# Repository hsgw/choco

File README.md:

# CHOCO

7x4 ortholinear onehanded keyboard/macropad.   

- kailh choc switch (pg1350)
- USB type-c
- STM32F072C8T6
- QMK Firmware - https://github.com/hsgw/qmk_firmware/tree/choco

## BUILD
### Cut mounting leg (SW_CHOC6)

### How to enter bootloader
1. Push and hold reset switch
2. Push and hold boot switch (SW_CHOC7 / right upper corner switch)
3. Release reset switch
4. Release boot switch

### Firmware
QMK Firmware - https://github.com/hsgw/qmk_firmware/tree/choco

## License
MIT license   
(c)2019 Takuya Urakawa, Dm9Records

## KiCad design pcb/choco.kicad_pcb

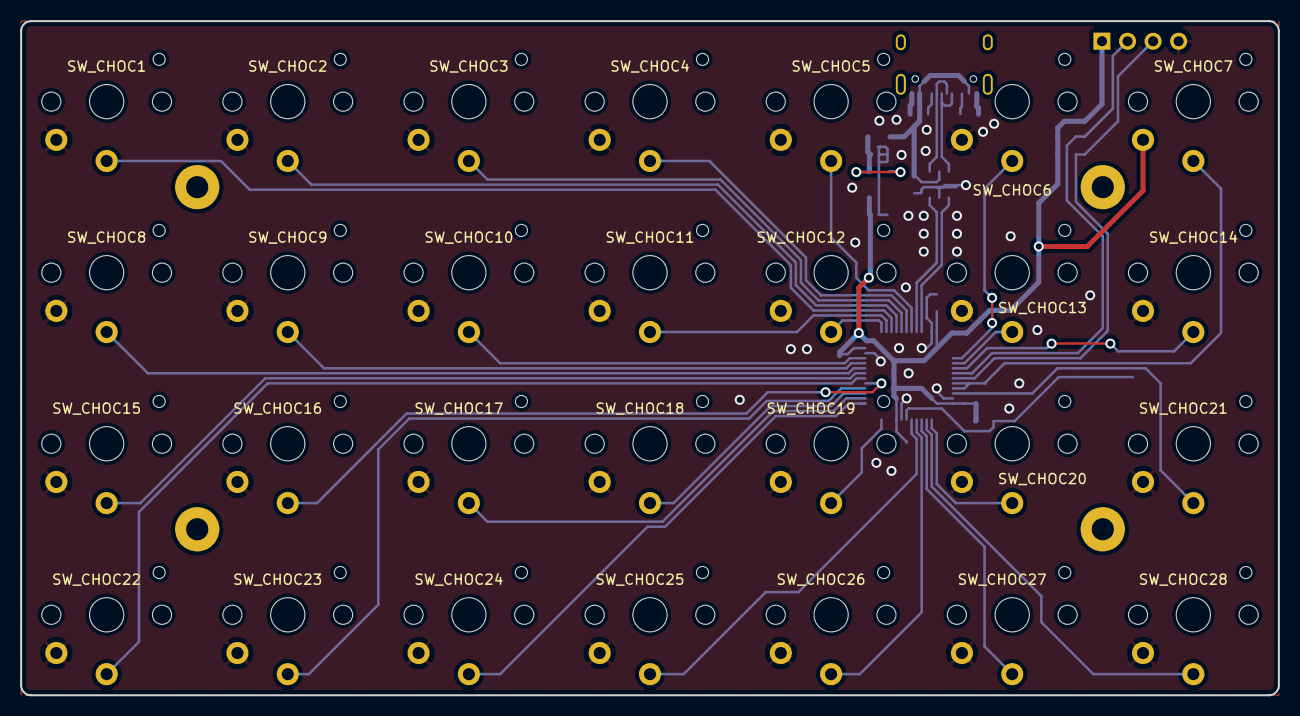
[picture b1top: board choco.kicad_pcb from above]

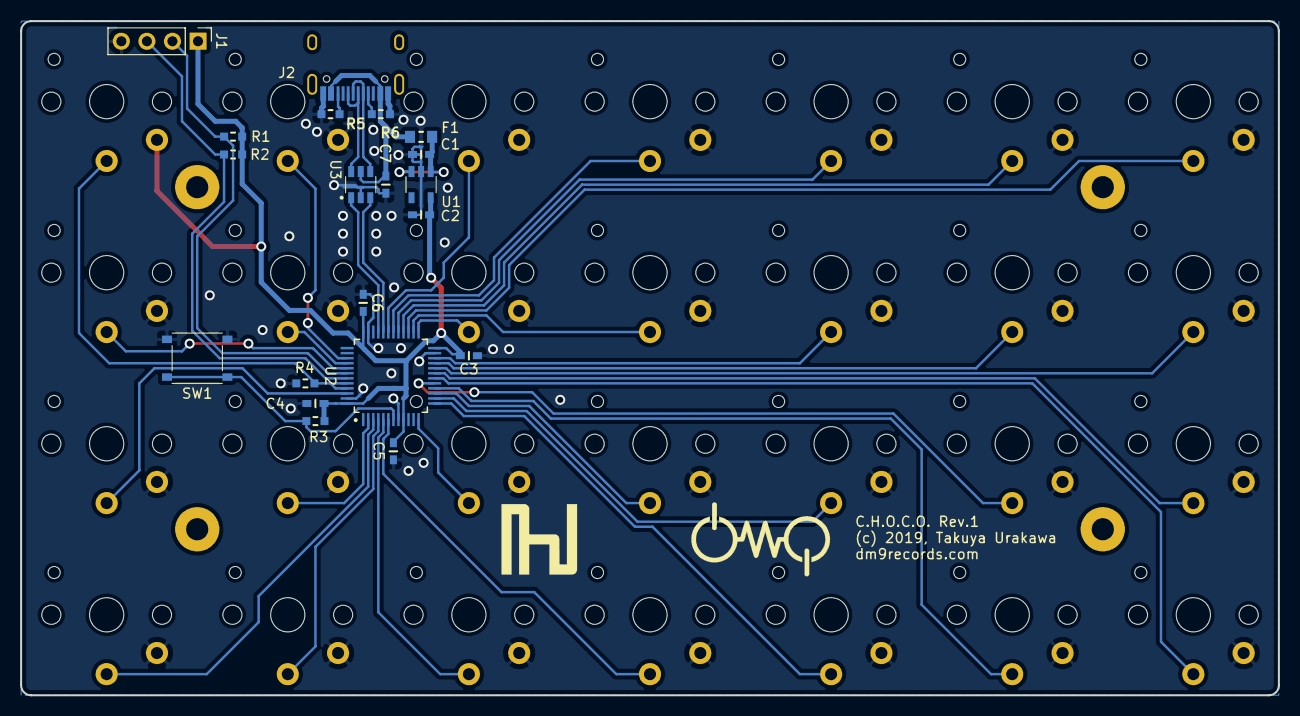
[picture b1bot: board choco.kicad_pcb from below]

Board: 2 copper layers, 125.0 x 67.0 mm, 48 parts (20 on the bottom side), 41 nets.

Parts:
C1, C2: 1u; C1608_Hand
C3, C4, C5, C6, C7: 0.1u; C1608_Hand
F1: 100mA; C2012_hand
J1: Conn_01x04; Socket_Strip_Straight_1x04_Pitch2.54mm
J2: USB_C_12pin_Receptacle; HRO-TYPE-C-31-M-12-Assembly
R1, R2: I2C; R1608_Hand
R3, R4: 10k; R1608_Hand
R5, R6: 5.1k; R1608_Hand
SW1: SW_Push; TACT_5.1x5.1
SW_CHOC1, SW_CHOC2, SW_CHOC3, SW_CHOC4, SW_CHOC5, SW_CHOC6, SW_CHOC7, SW_CHOC8, SW_CHOC9, SW_CHOC10, SW_CHOC11, SW_CHOC12, SW_CHOC13, SW_CHOC14, SW_CHOC15, SW_CHOC16, SW_CHOC17, SW_CHOC18, SW_CHOC19, SW_CHOC20, SW_CHOC21, SW_CHOC22, SW_CHOC23, SW_CHOC24, SW_CHOC25, SW_CHOC26, SW_CHOC27, SW_CHOC28: SW_Push; SW_kailh_pg1350_1u
U1: TLV73333PDBVR; SOT-23-5
U2: STM32F072C8Tx; LQFP-48_7x7mm_Pitch0.5mm
U3: USBLC6-2SC6; SOT-23-6

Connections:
+3V3: C2.1, C3.1, C4.1, C5.1, C6.1, J1.1, R1.1, R2.1, R3.1, SW_CHOC7.2, U1.5, U2.9, U2.24, U2.36, U2.48
/BOOT: R4.1, SW_CHOC7.1, U2.44, U2.45
/I2C_SCL: J1.2, R1.2, U2.42
/I2C_SDA: J1.3, R2.2, U2.43
/SW1: SW_CHOC1.1, U2.27
/SW2: SW_CHOC2.1, U2.28
/SW3: SW_CHOC3.1, U2.29
/SW4: SW_CHOC4.1, U2.30
/SW5: SW_CHOC5.1, U2.31
/SW6: SW_CHOC6.1, U2.39
/SW8: SW_CHOC8.1, U2.20
/SW9: SW_CHOC9.1, U2.21
/SW10: SW_CHOC10.1, U2.22
/SW11: SW_CHOC11.1, U2.26
/SW12: SW_CHOC12.1, U2.25
/SW13: SW_CHOC13.1, U2.40
/SW14: SW_CHOC14.1, U2.41
/SW15: SW_CHOC15.1, U2.19
/SW16: SW_CHOC16.1, U2.17
/SW17: SW_CHOC17.1, U2.14
/SW18: SW_CHOC18.1, U2.15
/SW19: SW_CHOC19.1, U2.12
/SW20: SW_CHOC20.1, U2.2
/SW21: SW_CHOC21.1, U2.46
/SW22: SW_CHOC22.1, U2.18
/SW23: SW_CHOC23.1, U2.16
/SW24: SW_CHOC24.1, U2.13
/SW25: SW_CHOC25.1, U2.6
/SW26: SW_CHOC26.1, U2.5
/SW27: SW_CHOC27.1, U2.4
/SW28: SW_CHOC28.1, U2.3
/USB_D+: U2.33, U3.1
/USB_D-: U2.32, U3.3
/USB_IN_D+: J2.A6, J2.B6, U3.6
/USB_IN_D-: J2.A7, J2.B7, U3.4
GND: C1.2, C2.2, C3.2, C4.2, C5.2, C6.2, C7.2, J1.4, J2.A1_B12, J2.B1_A12, R4.2, R5.2, R6.2, SW1.1, SW_CHOC1.2, SW_CHOC2.2, SW_CHOC3.2, SW_CHOC4.2, SW_CHOC5.2, SW_CHOC6.2, SW_CHOC8.2, SW_CHOC9.2, SW_CHOC10.2, SW_CHOC11.2, SW_CHOC12.2, SW_CHOC13.2, SW_CHOC14.2, SW_CHOC15.2, SW_CHOC16.2, SW_CHOC17.2, SW_CHOC18.2, SW_CHOC19.2, SW_CHOC20.2, SW_CHOC21.2, SW_CHOC22.2, SW_CHOC23.2, SW_CHOC24.2, SW_CHOC25.2, SW_CHOC26.2, SW_CHOC27.2, SW_CHOC28.2, U1.2, U2.8, U2.23, U2.35, U2.47, U3.2
unnamed: C1.1, F1.1, U1.1, U1.3
unnamed: J2.A5, R6.1
unnamed: J2.B5, R5.1
unnamed: R3.2, SW1.2, U2.7
VBUS: C7.1, F1.2, J2.A4_B9, J2.A9_B4, U3.5

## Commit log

2019-05-20 1st commit
2019-05-20 add build tips
2019-05-20 Create LICENSE
